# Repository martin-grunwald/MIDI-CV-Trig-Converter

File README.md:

# MIDI-CV-Trig-Converter

# Zadání
Navrhněte a realizujte převodník rozhraní MIDI na řídicí signály analogových syntezátorů CV/Trig pro modulární systém Eurorack. Převodník bude umožňovat převod zpráv nota zapnuta/vypnuta, zpráv Pitch bend change a zpráv pro změnu kontroleru. Převodník bude disponovat polyfonními výstupy CV, Gate a Trig pro výšku tónu a stlačení klávesy a dalšími výstupy řídicího signálu CV pro kontrolery a bude umožňovat výběr MIDI kontrolru pro každý z těchto výstupů. Převodník bude také obsahovat výstupy Trig pro převod zpráv synchronizace MIDI Clock.

# Popis
Z MIDI inputu půjdou data do UART portu na STM32 (31250 baud). Zapíše se Note On, Note Off, Výška tónu, Pitch bend a Clock. Note On, Note Off a výšky tónu se uloží pro každý hlas zvlášť.
Polyfonie se může řídit jako round robin nebo last note priority.

Switchem se dají přepínat režimy:
1. 4 hlasy polyfonie a žádný výstup CV z MIDI CC
2. Monofonie a 3 výstupy CV z MIDI CC

Režimů bude nakonec možná víc, ale pak už by se všechno mělo řešit v softwaru. Akorát by se pak použil vícepólový přepínač.

MIDI clock běží na 24ppqn, takže v STM32 bude potřeba vydělit clock rate (na čtvrťovou nebo osminovou notu, podle toho, jak bude potřeba).

Z MCU modelů nejvhodněji vypadá STM32F405RG + 2 externí 12-bitové, dvoukanálové převodníky (MCP4922).

Rozsah CV a V/Oct bude 0 - 10 V, přičemž pitch bend se bude přičítat k výstupu, takže to se bude řídit softwarově.
Jestli bude na výstupu převodníku 0,33V (nebo 0,5V), tak se dá potom použít ještě buffer (OPA1612) a pokud by bylo potřeba, tak ještě jednoduchý RC filtr na vyhlazení průběhu napětí a ochranné diody.

Gate signály by mohly jít z GPIO a do MOSFETu 2N7002. MOSFETY by měly umožnit odebírat růyné namětí v závislosti na tom, jaké napětí je konkrétně potřeba na trigger/gate inputu na jiném modulu (většinou 5V/10V/12V).

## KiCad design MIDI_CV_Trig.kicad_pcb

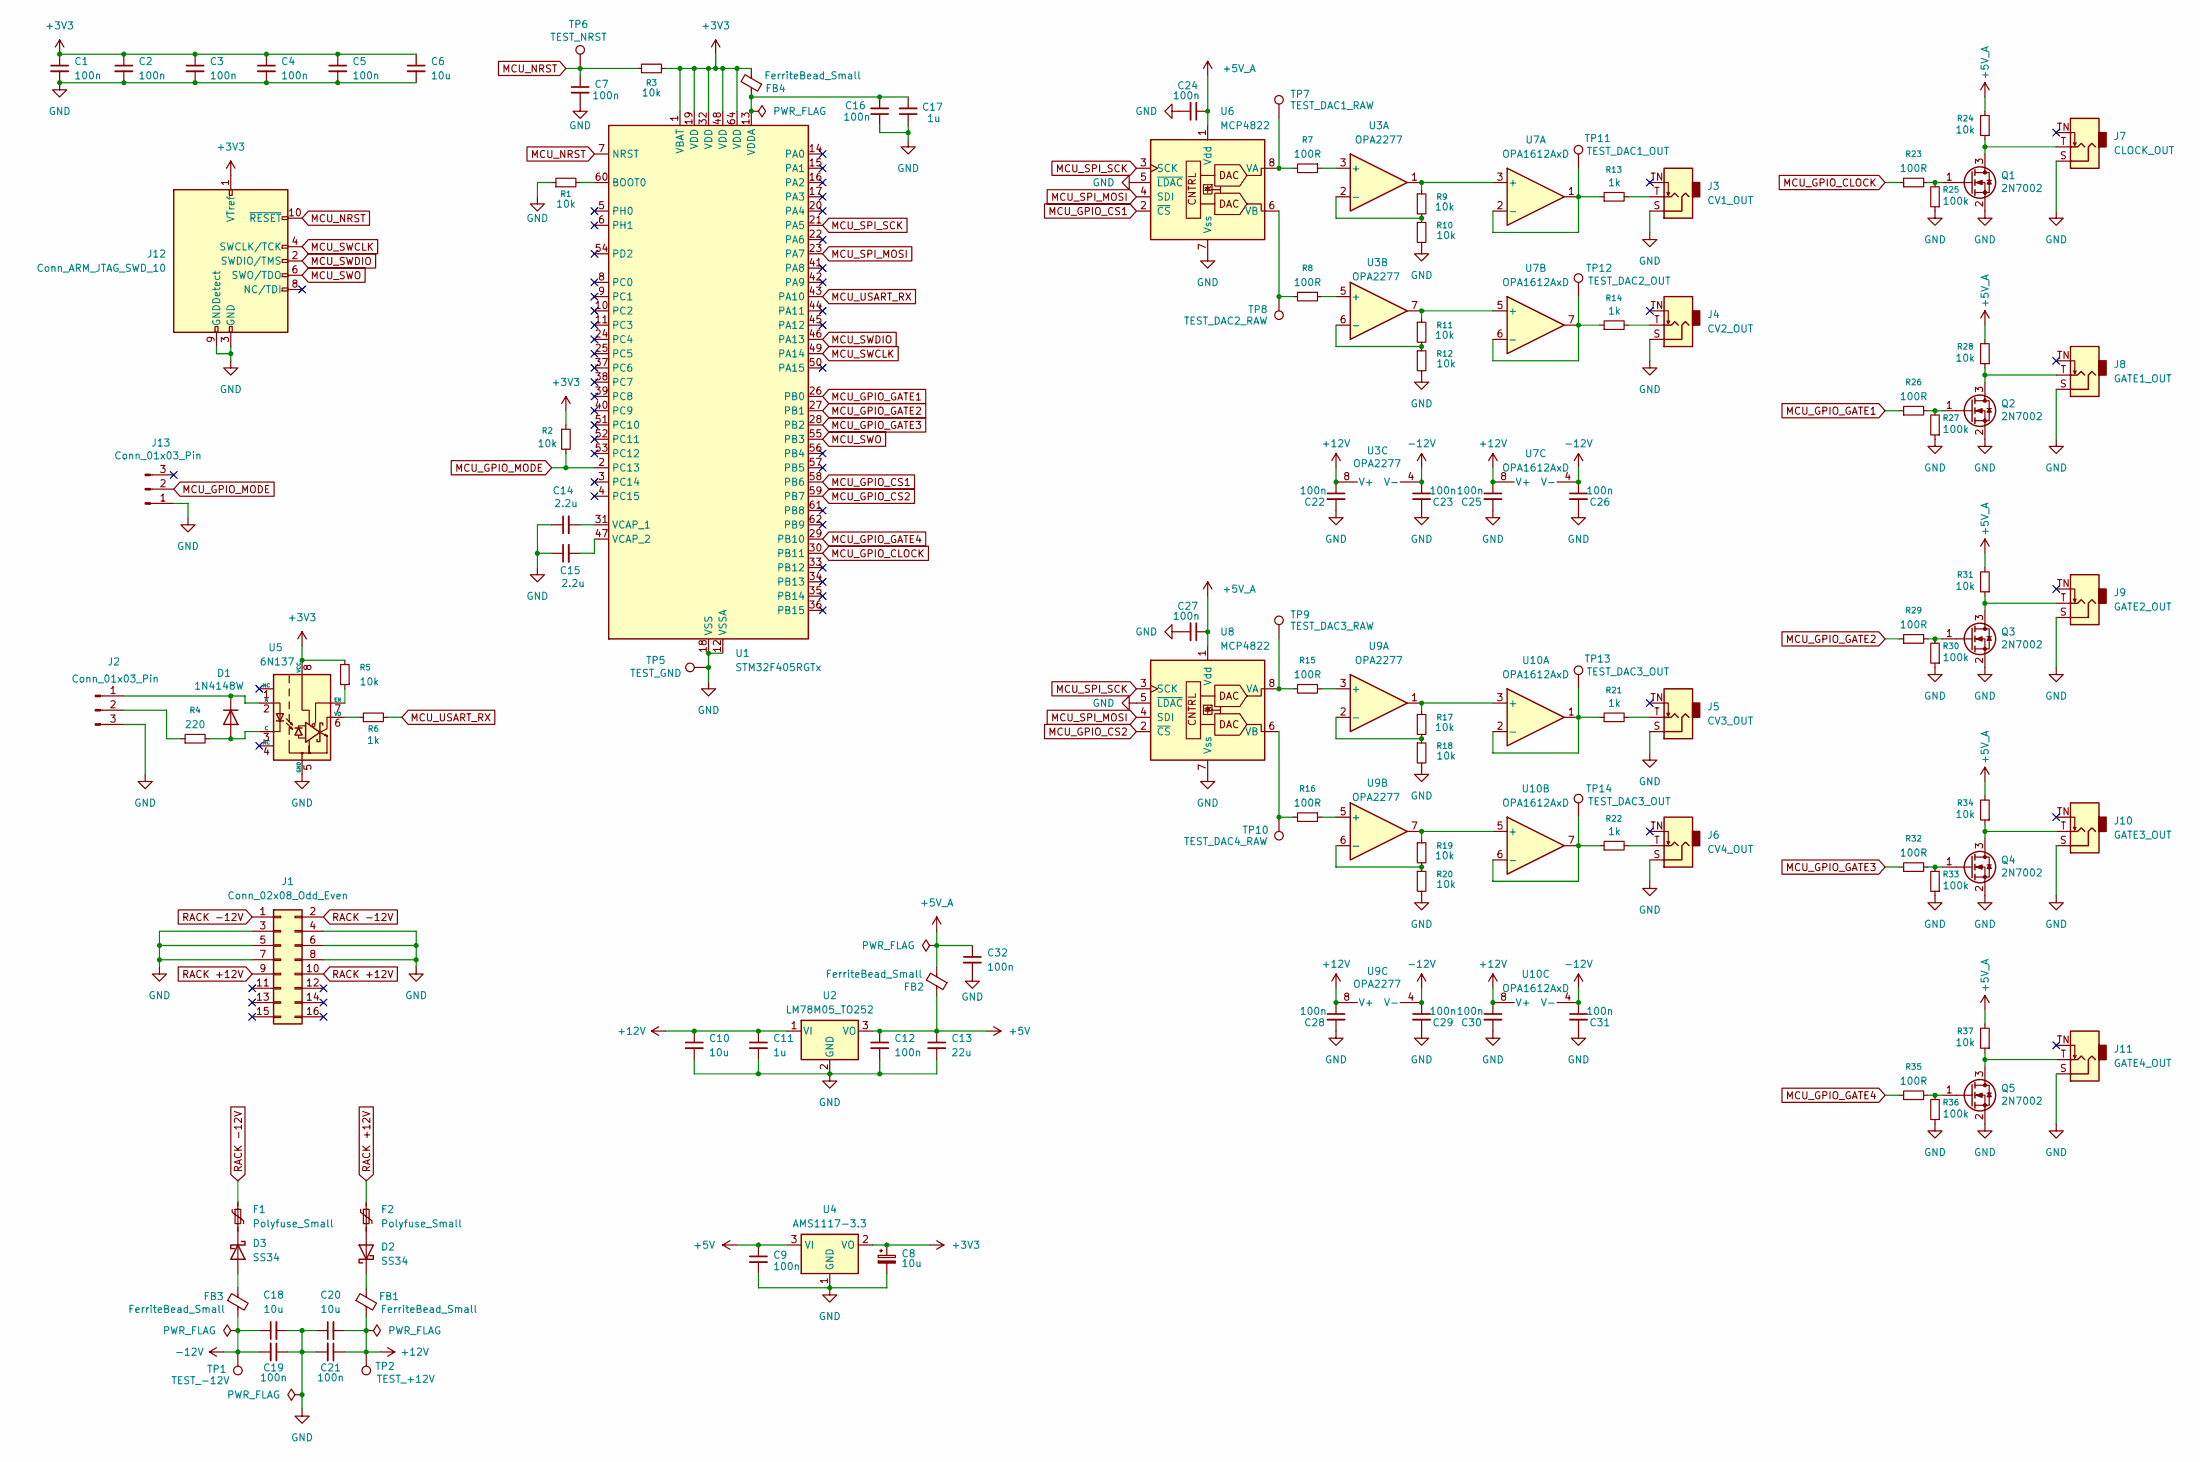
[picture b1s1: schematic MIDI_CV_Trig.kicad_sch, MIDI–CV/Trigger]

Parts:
C1, C2, C3, C4, C5, C7, C9, C12, C16, C22, C23, C24, C25, C26, C27, C28, C29, C30, C31, C32: 100n; C_0603_1608Metric; JLCPCB C14663
C6, C10, C18, C20: 10u; C_1206_3216Metric; JLCPCB C13585
C8: 10u; CP_EIA-3216-18_Kemet-A; JLCPCB C7171
C11, C17: 1u; C_0603_1608Metric; JLCPCB C15849
C13: 22u; C_1206_3216Metric; JLCPCB C12891
C14, C15: 2.2u; C_0603_1608Metric; JLCPCB C23630
C19, C21: 100n; C_1206_3216Metric; JLCPCB C14663
D1: 1N4148W; D_SOD-123; JLCPCB C2128
D2, D3: SS34; D_SMA; JLCPCB C8678
F1, F2: Polyfuse_Small; Fuse_1206_3216Metric; JLCPCB C70076
FB1, FB2, FB3, FB4: FerriteBead_Small; L_1206_3216Metric; JLCPCB C19330
J1: Conn_02x08_Odd_Even; IDC-Header_2x08_P2.54mm_Vertical
J2, J13: Conn_01x03_Pin; PinHeader_1x03_P2.54mm_Vertical
J3: CV1_OUT; Jack_3.5mm_QingPu_WQP-PJ398SM_Vertical_CircularHoles
J4: CV2_OUT; Jack_3.5mm_QingPu_WQP-PJ398SM_Vertical_CircularHoles
J5: CV3_OUT; Jack_3.5mm_QingPu_WQP-PJ398SM_Vertical_CircularHoles
J6: CV4_OUT; Jack_3.5mm_QingPu_WQP-PJ398SM_Vertical_CircularHoles
J7: CLOCK_OUT; Jack_3.5mm_QingPu_WQP-PJ398SM_Vertical_CircularHoles
J8: GATE1_OUT; Jack_3.5mm_QingPu_WQP-PJ398SM_Vertical_CircularHoles
J9: GATE2_OUT; Jack_3.5mm_QingPu_WQP-PJ398SM_Vertical_CircularHoles
J10: GATE3_OUT; Jack_3.5mm_QingPu_WQP-PJ398SM_Vertical_CircularHoles
J11: GATE4_OUT; Jack_3.5mm_QingPu_WQP-PJ398SM_Vertical_CircularHoles
J12: Conn_ARM_JTAG_SWD_10; PinHeader_2x05_P2.54mm_Vertical
Q1, Q2, Q3, Q4, Q5: 2N7002; SOT-23; JLCPCB C8545
R1, R2, R3, R5, R9, R10, R11, R12, R17, R18, R19, R20, R24, R28, R31, R34, R37: 10k; R_0603_1608Metric; JLCPCB C25804
R4: 220; R_0603_1608Metric; JLCPCB C23162
R6, R13, R14, R21, R22: 1k; R_0603_1608Metric; JLCPCB C21190
R7, R8, R15, R16, R23, R26, R29, R32, R35: 100R; R_0603_1608Metric; JLCPCB C22775
R25, R27, R30, R33, R36: 100k; R_0603_1608Metric; JLCPCB C25803
TP1: TEST_-12V; TestPoint_Pad_1.5x1.5mm
TP2: TEST_+12V; TestPoint_Pad_1.5x1.5mm
TP5: TEST_GND; TestPoint_Pad_2.5x2.5mm
TP6: TEST_NRST; TestPoint_Pad_1.5x1.5mm
TP7: TEST_DAC1_RAW; TestPoint_Pad_1.5x1.5mm
TP8: TEST_DAC2_RAW; TestPoint_Pad_1.5x1.5mm
TP9: TEST_DAC3_RAW; TestPoint_Pad_1.5x1.5mm
TP10: TEST_DAC4_RAW; TestPoint_Pad_1.5x1.5mm
TP11: TEST_DAC1_OUT; TestPoint_Pad_1.5x1.5mm
TP12: TEST_DAC2_OUT; TestPoint_Pad_1.5x1.5mm
TP13, TP14: TEST_DAC3_OUT; TestPoint_Pad_1.5x1.5mm
U1: STM32F405RGTx; LQFP-64_10x10mm_P0.5mm; JLCPCB C15742
U2: LM78M05_TO252; TO-252-2; JLCPCB C544492
U3, U9: OPA2277; SOIC-8_3.9x4.9mm_P1.27mm; JLCPCB C24460
U4: AMS1117-3.3; SOT-223-3_TabPin2; JLCPCB C6186
U5: 6N137; SMDIP-8_W7.62mm; JLCPCB C15825
U6, U8: MCP4822; SOIC-8_3.9x4.9mm_P1.27mm; JLCPCB C16040
U7, U10: OPA1612AxD; SOIC-8_3.9x4.9mm_P1.27mm; JLCPCB C94590

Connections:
+3V3: C1.1, C2.1, C3.1, C4.1, C5.1, C6.1, C8.1, FB4.2, J12.1 (VTref), R2.1, R3.2, R5.2, U1.1 (VBAT), U1.19 (VDD), U1.32 (VDD), U1.48 (VDD), U1.64 (VDD), U4.2 (VO), U5.8 (VCC)
+5V: C9.1, C12.1, C13.1, FB2.1, U2.3 (VO), U4.3 (VI)
+5V_A: C24.1, C27.1, C32.1, FB2.2, R24.2, R28.2, R31.2, R34.2, R37.2, U6.1 (Vdd), U8.1 (Vdd)
+12V: C10.1, C11.1, C20.2, C21.1, C22.1, C25.1, C28.1, C30.1, FB1.2, TP2.1, U2.1 (VI), U3.8 (V+), U7.8 (V+), U9.8 (V+), U10.8 (V+)
-12V: C18.1, C19.2, C23.1, C26.1, C29.1, C31.1, FB3.2, TP1.1, U3.4 (V-), U7.4 (V-), U9.4 (V-), U10.4 (V-)
GND: C1.2, C2.2, C3.2, C4.2, C5.2, C6.2, C7.2, C8.2, C9.2, C10.2, C11.2, C12.2, C13.2, C14.1, C15.1, C16.1, C17.1, C18.2, C19.1, C20.1, C21.2, C22.2, C23.2, C24.2, C25.2, C26.2, C27.2, C28.2, C29.2, C30.2, C31.2, C32.2, J1.3, J1.4, J1.5, J1.6, J1.7, J1.8, J2.3, J3.S, J4.S, J5.S, J6.S, J7.S, J8.S, J9.S, J10.S, J11.S, J12.3 (GND), J12.5 (GND), J12.9 (GNDDetect), J13.1, Q1.2 (S), Q2.2 (S), Q3.2 (S), Q4.2 (S), Q5.2 (S), R1.1, R10.2, R12.2, R18.2, R20.2, R25.1, R27.1, R30.1, R33.1, R36.1, TP5.1, U1.12 (VSSA), U1.18 (VSS), U1.63 (VSS), U2.2 (GND), U4.1 (GND), U5.5 (GND), U6.5 (~LDAC), U6.7 (Vss), U8.5 (~LDAC), U8.7 (Vss)
MCU_GPIO_CLOCK: R23.1, U1.30 (PB11)
MCU_GPIO_CS1: U1.58 (PB6), U6.2 (~CS)
MCU_GPIO_CS2: U1.59 (PB7), U8.2 (~CS)
MCU_GPIO_GATE1: R26.1, U1.26 (PB0)
MCU_GPIO_GATE2: R29.1, U1.27 (PB1)
MCU_GPIO_GATE3: R32.1, U1.28 (PB2)
MCU_GPIO_GATE4: R35.1, U1.29 (PB10)
MCU_GPIO_MODE: J13.2, R2.2, U1.2 (PC13)
MCU_NRST: C7.1, J12.10 (~RESET), R3.1, TP6.1, U1.7 (NRST)
MCU_SPI_MOSI: U1.23 (PA7), U6.4 (SDI), U8.4 (SDI)
MCU_SPI_SCK: U1.21 (PA5), U6.3 (SCK), U8.3 (SCK)
MCU_SWCLK: J12.4 (SWCLK/TCK), U1.49 (PA14)
MCU_SWDIO: J12.2 (SWDIO/TMS), U1.46 (PA13)
MCU_SWO: J12.6 (SWO/TDO), U1.55 (PB3)
MCU_USART_RX: R6.2, U1.43 (PA10)
unnamed: D1.2 (A), R4.2, U5.3 (C)
unnamed: D1.1 (K), J2.1, U5.2 (A)
unnamed: D2.2 (A), F2.2
unnamed: D2.1 (K), FB1.1
unnamed: D3.2 (A), FB3.1
unnamed: D3.1 (K), F1.2
unnamed: J2.2, R4.1
unnamed: J3.T, R13.2
unnamed: J4.T, R14.2
unnamed: J5.T, R21.2
unnamed: J6.T, R22.2
unnamed: J7.T, Q1.3 (D), R24.1
unnamed: Q1.1 (G), R23.2, R25.2
unnamed: J8.T, Q2.3 (D), R28.1
unnamed: Q2.1 (G), R26.2, R27.2
unnamed: J9.T, Q3.3 (D), R31.1
unnamed: Q3.1 (G), R29.2, R30.2
unnamed: J10.T, Q4.3 (D), R34.1
unnamed: Q4.1 (G), R32.2, R33.2
unnamed: J11.T, Q5.3 (D), R37.1
unnamed: Q5.1 (G), R35.2, R36.2
unnamed: R1.2, U1.60 (BOOT0)
unnamed: C14.2, U1.31 (VCAP_1)
unnamed: C15.2, U1.47 (VCAP_2)
unnamed: C16.2, C17.2, FB4.1, U1.13 (VDDA)
unnamed: R7.1, U3.3 (+)
unnamed: R9.2, R10.1, U3.2 (-)
unnamed: R8.1, U3.5 (+)
unnamed: R11.2, R12.1, U3.6 (-)
unnamed: R5.1, U5.7 (EN)
unnamed: R6.1, U5.6 (VO)
unnamed: R7.2, TP7.1, U6.8 (VA)
unnamed: R8.2, TP8.1, U6.6 (VB)
unnamed: R9.1, U3.1, U7.3 (+)
unnamed: R13.1, TP11.1, U7.1, U7.2 (-)
unnamed: R11.1, U3.7, U7.5 (+)
unnamed: R14.1, TP12.1, U7.6 (-), U7.7
unnamed: R15.2, TP9.1, U8.8 (VA)
unnamed: R16.2, TP10.1, U8.6 (VB)
unnamed: R15.1, U9.3 (+)
unnamed: R17.2, R18.1, U9.2 (-)
unnamed: R16.1, U9.5 (+)
unnamed: R19.2, R20.1, U9.6 (-)
unnamed: R17.1, U9.1, U10.3 (+)
unnamed: R21.1, TP13.1, U10.1, U10.2 (-)
unnamed: R19.1, U9.7, U10.5 (+)
unnamed: R22.1, TP14.1, U10.6 (-), U10.7
RACK +12V: F2.1, J1.9, J1.10
RACK -12V: F1.1, J1.1, J1.2

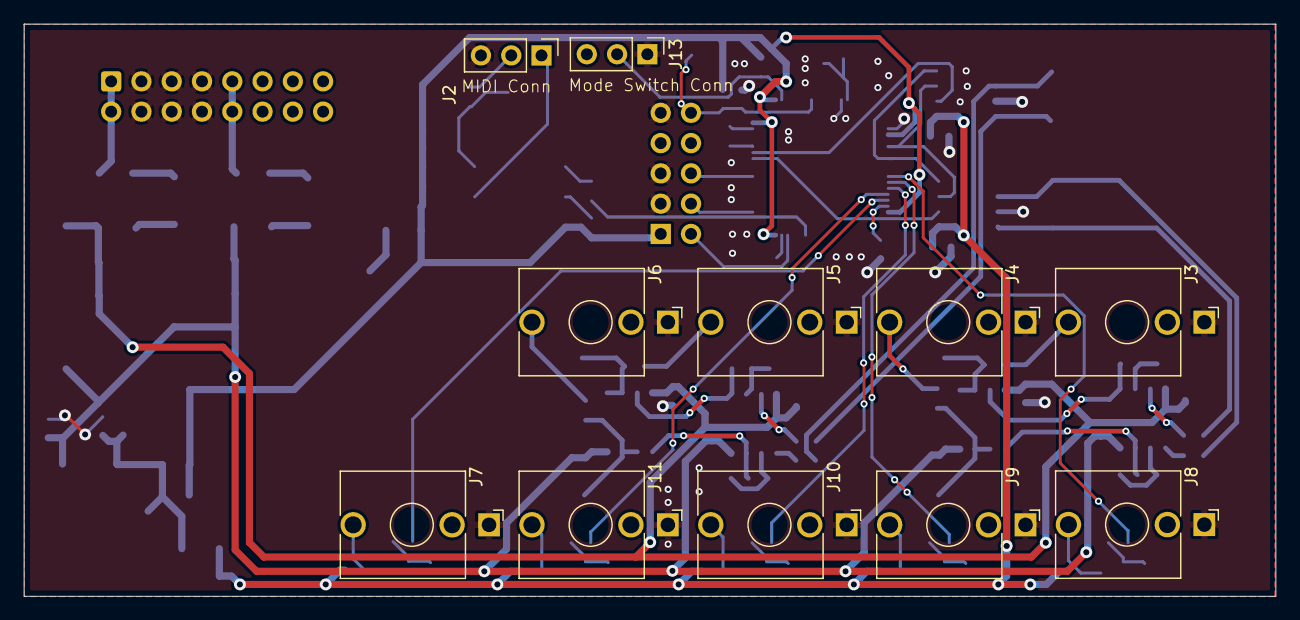
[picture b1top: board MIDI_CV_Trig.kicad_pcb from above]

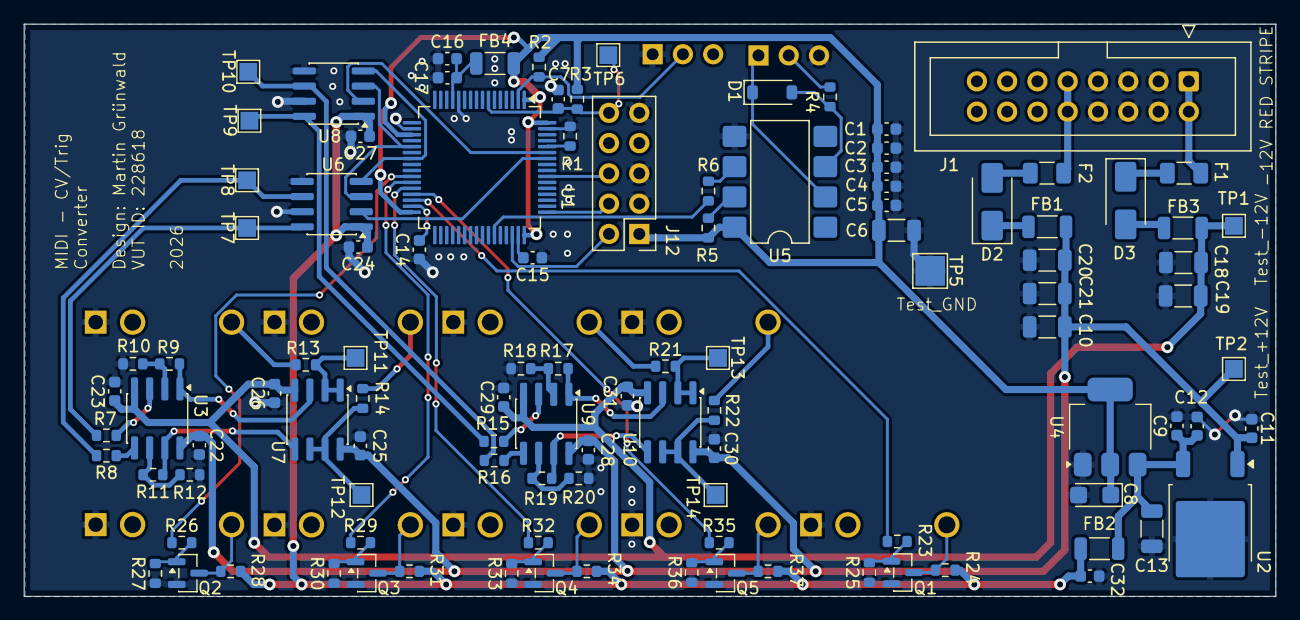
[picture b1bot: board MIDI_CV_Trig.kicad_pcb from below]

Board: 2 copper layers, 105.0 x 48.0 mm, 118 parts (107 on the bottom side), 70 nets.

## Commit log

2025-12-07 Add images for gate signal and MOSFET explanation
    Added images to illustrate gate signal and MOSFET usage.
2026-04-20 Remove images from README
    Removed two images from the README file.
